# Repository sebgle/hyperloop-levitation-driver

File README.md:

# Hyperloop Levitation Coil Driver

A two-channel H-bridge driver for the levitation coils on a hyperloop pod. It takes PWM from the
pod's control computer and switches 60 V into two coils at up to 30 A each, roughly 1.8 kW per
coil. Two boards drive the pod's four coils.

Design work for the levitation subsystem of a student hyperloop pod. The levitation team set the
requirements. The schematic, board layout, documentation and verification scripts are mine. This
repository holds the KiCad 10 project along with the design notes, the reviews, and the scripts
that check the layout.

**Status: schematic done and verified. Placement done. Routing under way.**

## Requirements

| | |
|---|---|
| Bus | 60 V max, battery fed |
| Current | 30 A per coil by design. The team's stated minimum is 60 A across all four |
| Coil | About 2 Ω and 10 mH, unmeasured |
| PWM | 16 kHz now, 32 kHz ceiling |
| Control | PID runs on a separate MCU. This board takes PWM and a shutdown line |
| Grounding | Coils float. Only common point is the motor controller negatives |
| Rails | Pod supplies 12 V, 5 V and 3.3 V |

## The board

| | |
|---|---|
| Size | 160 × 140 mm, 4 layers, 2 oz outer / 1 oz inner |
| Parts | 184 footprints, 99 nets, 492 pads |
| FETs | 8 × IRF100B201, 100 V, 4.2 mΩ, TO-220 on a shared heatsink |
| Gate drive | 4 × IR2184, bootstrap high side |
| Sensing | 0.5 mΩ shunt in line with each coil, INA240A2 amplifier |
| Protection | ±45 A window comparator into a latch on the driver shutdown pin |
| Bus | 6 × 470 µF, ceramics at each bridge, TVS clamp |
| Connectors | Molex 38969-0002, 50 A, takes 8 AWG |

## Design decisions

### Modulation

Four transistors form an H-bridge with the coil across the middle. Which pair is switched on
decides what the coil sees.

The board cycles through these states thousands of times a second. What sets the average voltage
across the coil is which states it cycles between, and how long it holds each one.

There are two ways to pick that sequence:

```
locked antiphase   Q1+Q4 -> Q2+Q3 -> Q1+Q4 -> Q2+Q3    coil sees  +60 V, -60 V, +60 V, -60 V
unipolar           Q1+Q4 -> Q1+Q3 -> Q1+Q4 -> Q1+Q3    coil sees  +60 V,   0 V, +60 V,   0 V
```

Antiphase only uses the top two rows of the table, so the coil gets slammed between +60 V and
−60 V every cycle even when you want very little current out of it. Unipolar swaps one of those
for a freewheel row, where both ends of the coil are held at the same voltage. Nothing is
pushing the current any more, so it coasts around a loop through the two transistors and fades
slowly, the way a bike wheel spins on after you stop pedalling. A switching cycle is far too
short for it to fade much. That halves the voltage swing, and at low output the coil spends most
of each cycle coasting.

That keeps the current steadier and takes a lot of strain off the bus capacitors, which is what
decided it. A levitation coil sits near zero most of the time, so low output is its normal
operating point.

The tradeoff is that the four transistors no longer share the work evenly. Two do most of it and
run hot, two do very little and stay cool. They are arranged alternately on the heatsink so no
two hot ones sit next to each other.

### Four layers

A four-layer board costs more than a two-layer one, and the usual justification for the extra
layers, less resistance in the copper, did not apply. The power traces here are already wide
enough, and a third copper layer would save about 3 W out of 54 W.

The real reason is what sits underneath the transistors. On a four-layer board a solid ground
layer sits 0.2 mm below them instead of 1.44 mm away on the other side of the board. Current
returning through that nearby layer takes a much tighter path, which shrinks the voltage spikes
the transistors see each time they switch. The same layer shields the small measurement signals
from the 30 A being chopped a couple of centimetres away.

### Current sensing

Each coil's current is measured across a very small resistor, half a milliohm, which turns 30 A
into about 15 millivolts. An amplifier scales that up fifty times to something the rest of the
circuit can work with. The resistor sits in the wire feeding the coil rather than in the ground
return, because current in a levitation coil flows in both directions and this is the only
position that sees both. TI's application note SBOA174 covers why this amplifier suits the job.

### Overcurrent protection

If coil current passes 45 A in either direction, a comparator trips and a latch shuts the gate
drivers off and holds them off until the microcontroller clears it. Without the latch the fault
would clear itself the moment current dropped, and the board would switch on and off
repeatedly. The comparator takes 1.3 microseconds to react, which sounded far too slow until I
worked out how fast the current can actually change: the coil's inductance limits it to about
13 milliamps in that time. The genuinely fast failure is both transistors in one leg turning on
together, and the gate driver chips block that on their own.

## Checking the layout

Instead of trusting measurements written down by hand, a script reads the board file and
recalculates them. Every spacing and clearance figure quoted in the documentation comes out of
it, and it runs in about a second.

```
courtyard overlaps: 0
CH1 A   12.9 mm    CH1 B   16.7 mm
CH2 A   12.9 mm    CH2 B   16.7 mm
heatsink-shadow intrusions: none
```

The wiring was also checked against the connection list exported from the schematic, separately
from KiCad's own checker, and matched exactly on all 99 nets and 492 pads. Two rules that used
to live in a document now live in the board's rule file, so the software refuses to let me break
them: high-current nets have to be poured as wide copper areas rather than drawn as thin traces,
and the inner ground layer stays solid.

## Assumptions

Some inputs to this design were never measured, so every assumption is written down with what
happens if it turns out wrong. The full list, A1 to A16, is in `docs/09_design_sheet_rev0.md`.
Three of them matter:

- **A1**: the coil is 2 Ω. If it is really 4 Ω, the board can only push half the current and the
  high-side gate drive stops working. Nobody has put a meter on it yet.
- **A9**: 60 V is the maximum, not the normal running voltage. If it is the normal voltage, a
  full battery sits closer to 67 V and the 100 V parts get uncomfortably close to their limit.
- **A16**: the power traces are 10.7 mm wide. That figure comes from an older standard, and the
  project notes already say it should be rechecked against the current one.

## Mistakes and what they changed

**Measured the wrong thing.** Six large capacitors were supposed to fit between the two coil
connectors. Comparing the metal pads, they fit. Comparing the space each part actually needs
around it, they did not, because the connector needs far more room than its pads suggest. The
board grew from 160 × 100 to 160 × 140 mm, and I rewrote the checker to use the real keep-out
areas.

**Dropped a digit.** The board file said the copper was 0.007 mm thick instead of 0.07 mm.
Nothing inside KiCad depended on it, but it would have gone to the manufacturer, and at that
thickness the power traces would have run ten times hotter than intended.

**Trusted a number that looked deliberate.** The high-current traces were set to 3 mm wide,
which looks like a real power width. At 30 A that works out to roughly a 160 °C rise. It needed
about eight times more copper than that. The same setting had also caught ground, so all 119
ground pads inherited it.

**Reviewed in the wrong order.** Three rounds of review found 19, then 5, then 14 problems, and
about 40 % of the last round came from fixes made in the first two. Patching a design whose main
input is still unmeasured creates problems faster than review finds them, so I stopped and moved
on to layout.

## Repository layout

```
final_lev.kicad_*                KiCad project and its custom design rules
lib.pretty/                      custom connector footprint
tools/lay.py                     the layout checker
docs/00_design_log.md            running log, including the corrections
docs/01_reference_library.md     every datasheet and app note used, each one checked
docs/09_design_sheet_rev0.md     component values and the assumption list
docs/16_adversarial_review.md    38 review findings across three rounds
docs/18_firmware_interface.md    what the control microcontroller has to send
docs/20_layout_phase.md          placement and the verified clearances
docs/21_stackup_and_layers.md    layer stackup and routing order
```

## Not done

- Routing. The inner ground layer is poured, nothing else is.
- The coil has never been measured. Once it is, several numbers have to be redone together,
  because they all depend on it: ripple, transistor heating, heatsink size, gate drive supply
  and trip timing.
- Some heat calculations in `docs/09` were done under the older switching scheme.
- The bus fault detector is specified and not designed.
- `docs/09` still lists an older set of current-sense parts. The schematic is right and that
  document is stale.

## Running it

KiCad 10 on Windows. The scripts are Python 3, standard library only. From the project root:

```powershell
py tools\lay.py
```

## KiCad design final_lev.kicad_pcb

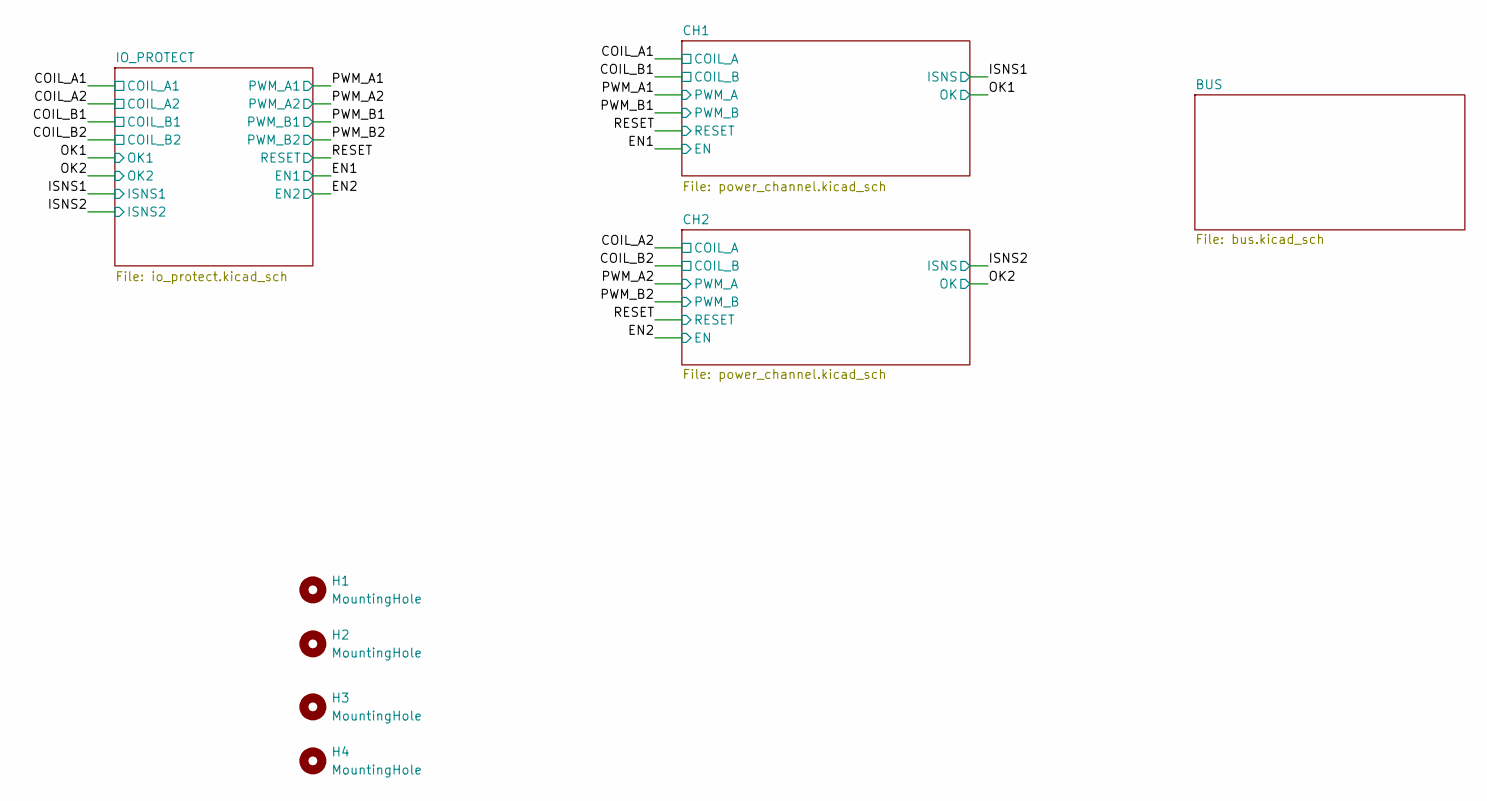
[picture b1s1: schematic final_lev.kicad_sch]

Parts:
H1, H2, H3, H4: MountingHole; MountingHole_3.2mm_M3_Pad

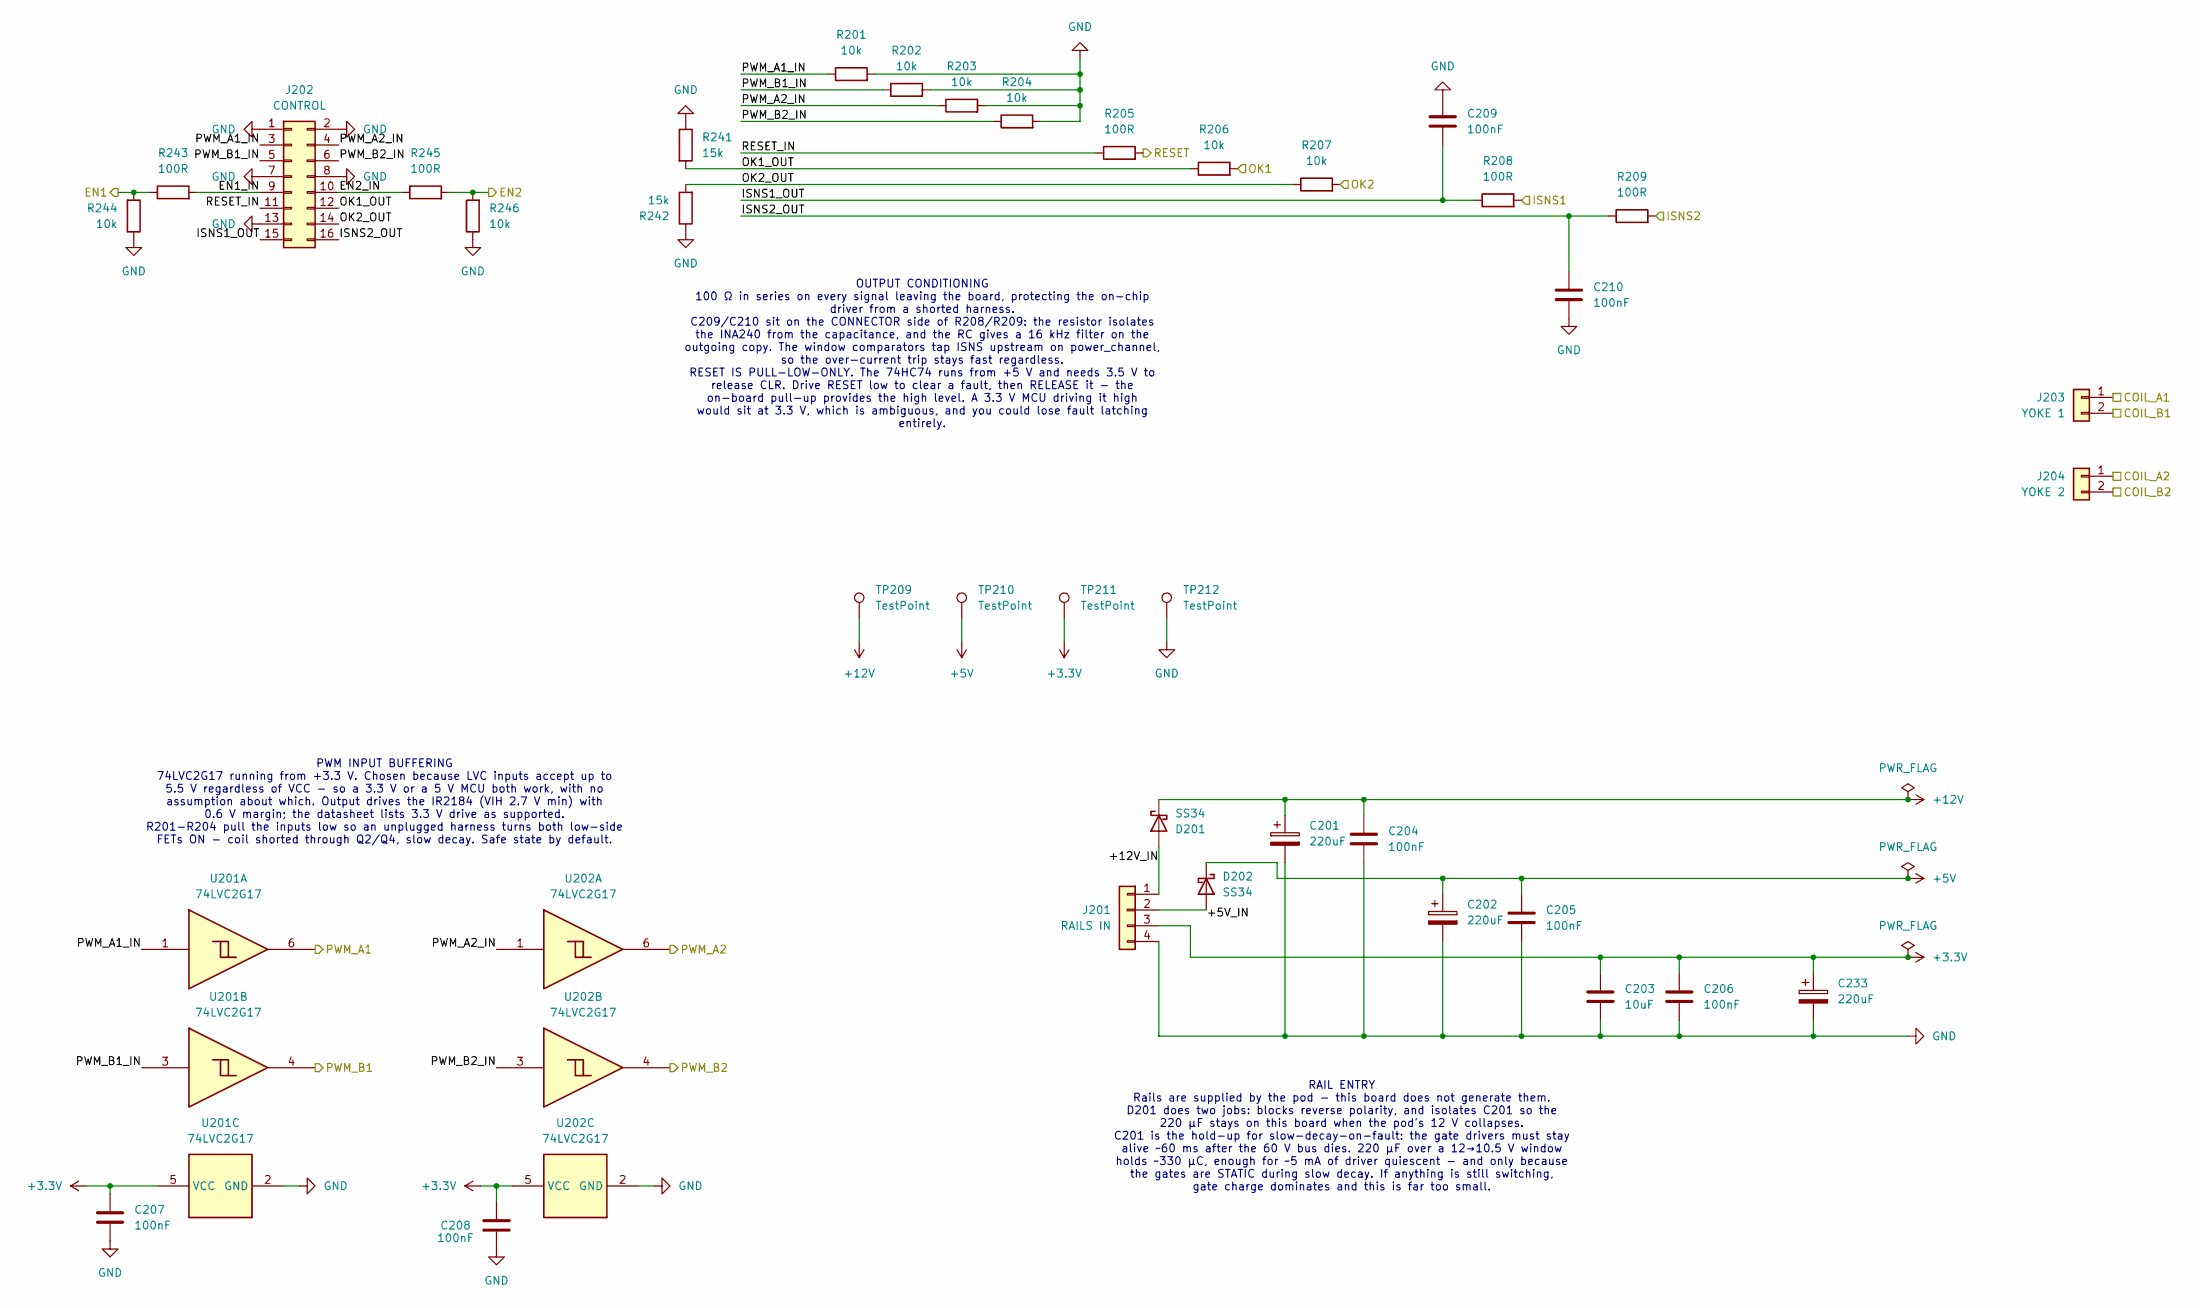
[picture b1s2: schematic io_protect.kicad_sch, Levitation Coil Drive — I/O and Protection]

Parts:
C201, C202, C233: 220uF; CP_Radial_D8.0mm_P3.50mm; Voltage 25V
C203: 10uF; C_1206_3216Metric_Pad1.33x1.80mm_HandSolder; Voltage 25V
C204, C205, C206, C207, C208, C209, C210: 100nF; C_0805_2012Metric_Pad1.18x1.45mm_HandSolder; Voltage 25V
D201, D202: SS34; D_SMA_Handsoldering
J201: RAILS IN; Molex_Micro-Fit_3.0_43650-0400_1x04_P3.00mm_Horizontal; MPN 43650-0400
J202: CONTROL; Molex_Micro-Fit_3.0_43045-1600_2x08_P3.00mm_Horizontal; MPN 43045-1600
J203: YOKE 1; 389690002; MPN 38969-0002
J204: YOKE 2; 389690002; MPN 38969-0002
R201, R202, R203, R204, R206, R207, R244, R246: 10k; R_0805_2012Metric_Pad1.20x1.40mm_HandSolder
R205, R208, R209, R243, R245: 100R; R_0805_2012Metric_Pad1.20x1.40mm_HandSolder
R241, R242: 15k; R_0805_2012Metric_Pad1.20x1.40mm_HandSolder
TP209, TP210, TP211, TP212: TestPoint; TestPoint_Loop_D2.50mm_Drill1.0mm
U201, U202: 74LVC2G17; SOT-23-6

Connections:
+3.3V: C203.1, C206.1, C207.1, C208.1, C233.1, J201.3, TP211.1 (1_1), U201.5 (VCC), U202.5 (VCC); also elsewhere on the board
+5V: C202.1, C205.1, D202.1 (K), TP210.1 (1_1); also elsewhere on the board
+12V: C201.1, C204.1, D201.1 (K), TP209.1 (1_1); also elsewhere on the board
/COIL_A1: J203.1; also elsewhere on the board
/COIL_A2: J204.1; also elsewhere on the board
/COIL_B1: J203.2; also elsewhere on the board
/COIL_B2: J204.2; also elsewhere on the board
/EN1: R243.1, R244.2; also elsewhere on the board
/EN2: R245.2, R246.2; also elsewhere on the board
/IO_PROTECT/+5V_IN: D202.2 (A), J201.2
/IO_PROTECT/+12V_IN: D201.2 (A), J201.1
/IO_PROTECT/EN1_IN: J202.9, R243.2
/IO_PROTECT/EN2_IN: J202.10, R245.1
/IO_PROTECT/ISNS1_OUT: C209.2, J202.15, R208.1
/IO_PROTECT/ISNS2_OUT: C210.1, J202.16, R209.1
/IO_PROTECT/OK1_OUT: J202.12, R206.1, R241.2
/IO_PROTECT/OK2_OUT: J202.14, R207.1, R242.2
/IO_PROTECT/PWM_A1_IN: J202.3, R201.1, U201.1
/IO_PROTECT/PWM_A2_IN: J202.4, R203.1, U202.1
/IO_PROTECT/PWM_B1_IN: J202.5, R202.1, U201.3
/IO_PROTECT/PWM_B2_IN: J202.6, R204.1, U202.3
/IO_PROTECT/RESET_IN: J202.11, R205.1
/ISNS1: R208.2; also elsewhere on the board
/ISNS2: R209.2; also elsewhere on the board
/OK1: R206.2; also elsewhere on the board
/OK2: R207.2; also elsewhere on the board
/PWM_A1: U201.6; also elsewhere on the board
/PWM_A2: U202.6; also elsewhere on the board
/PWM_B1: U201.4; also elsewhere on the board
/PWM_B2: U202.4; also elsewhere on the board
/RESET: R205.2; also elsewhere on the board
GND: C201.2, C202.2, C203.2, C204.2, C205.2, C206.2, C207.2, C208.2, C209.1, C210.2, C233.2, J201.4, J202.1, J202.2, J202.7, J202.8, J202.13, R201.2, R202.2, R203.2, R204.2, R241.1, R242.1, R244.1, R246.1, TP212.1 (1_1), U201.2 (GND), U202.2 (GND); also elsewhere on the board

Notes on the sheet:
PWM INPUT BUFFERING 74LVC2G17 running from +3.3 V. Chosen because LVC inputs accept up to 5.5 V regardless of VCC - so a 3.3 V or a 5 V MCU both work, with no assumption about which. Output drives the IR2184 (VIH 2.7 V min) with 0.6 V margin; the datasheet lists 3.3 V drive as supported. R201-R204 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
RAIL ENTRY Rails are supplied by the pod - this board does not generate them. D201 does two jobs: blocks reverse polarity, and isolates C201 so the 220 µF stays on this board when the pod's 12 V collapses. C201 is the hold-up for slow-decay-on-fault: the gate drivers must stay alive ~60 ms after th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
OUTPUT CONDITIONING 100 Ω in series on every signal leaving the board, protecting the on-chip driver from a shorted harness. C209/C210 sit on the CONNECTOR side of R208/R209: the resistor isolates the INA240 from the capacitance, and the RC gives a 16 kHz filter on the outgoing copy. The window com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

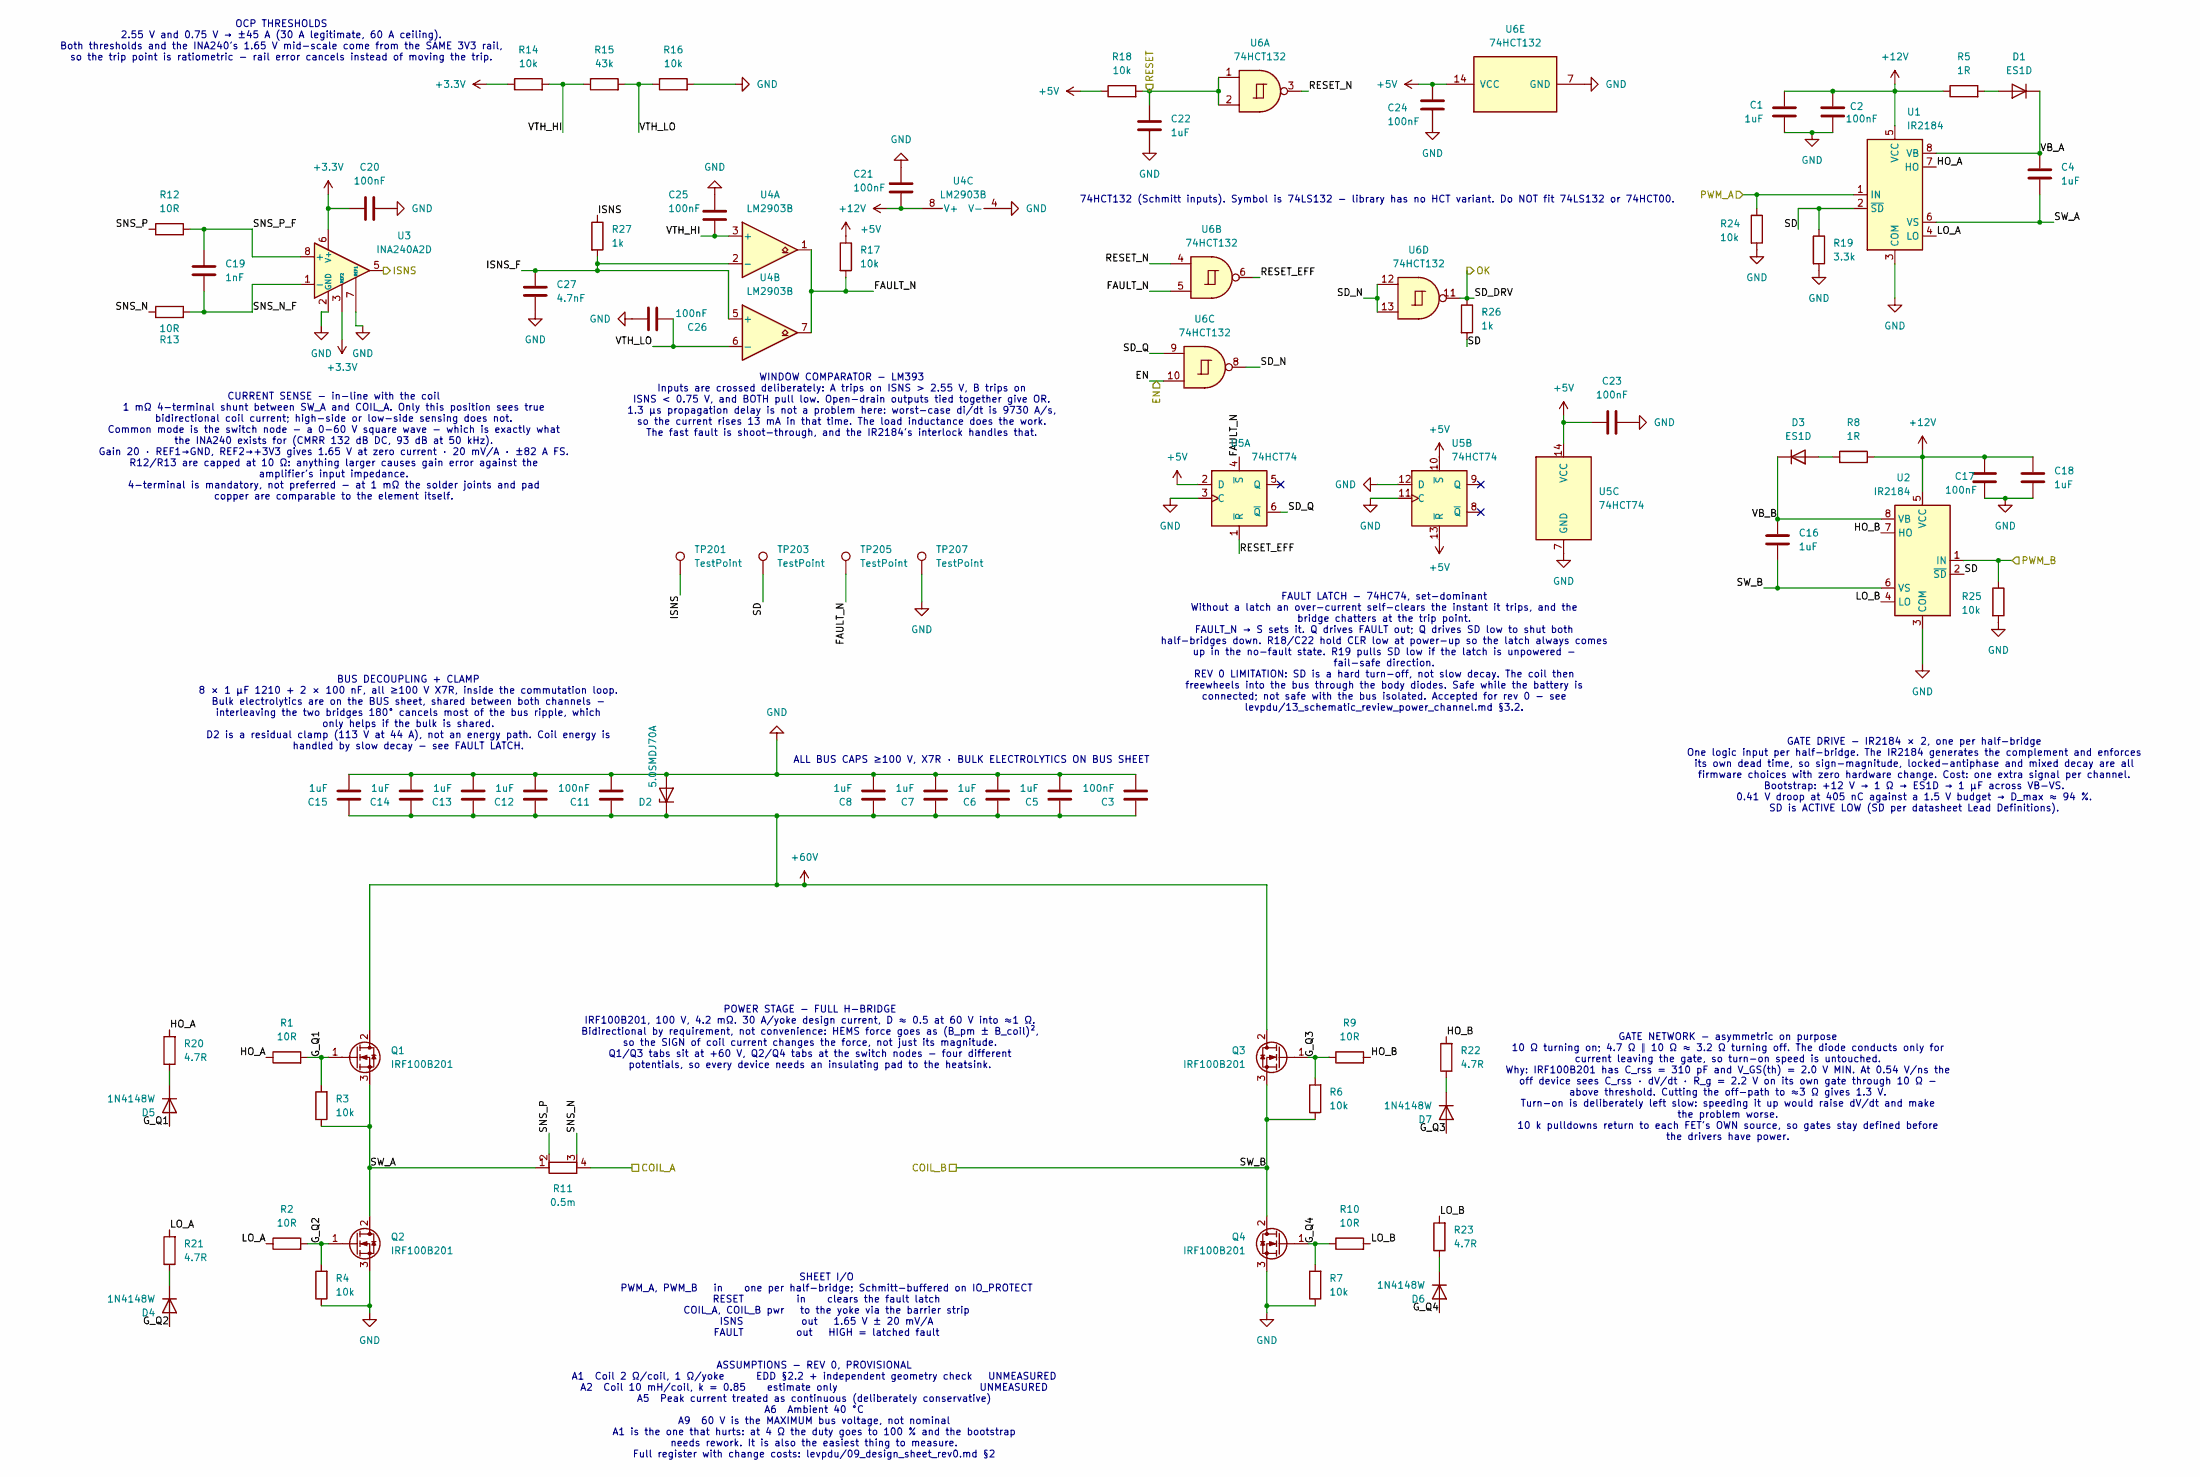
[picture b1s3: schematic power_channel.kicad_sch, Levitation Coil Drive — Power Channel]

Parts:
C1, C4, C16, C18, C22: 1uF; C_0805_2012Metric_Pad1.18x1.45mm_HandSolder; Voltage 25V
C2, C3, C11, C17, C20, C21, C23: 100nF; C_0805_2012Metric_Pad1.18x1.45mm_HandSolder; Voltage 100V
C5, C6, C7, C8, C12, C13, C14, C15: 1uF; C_1210_3225Metric_Pad1.33x2.70mm_HandSolder; Voltage 100V
C19: 1nF; C_0805_2012Metric_Pad1.18x1.45mm_HandSolder; Voltage 50V
C24, C25, C26: 100nF; C_0805_2012Metric_Pad1.18x1.45mm_HandSolder; Voltage 25V
C27: 4.7nF; C_0805_2012Metric_Pad1.18x1.45mm_HandSolder; Voltage 50V
D1, D3: ES1D; D_SMA_Handsoldering
D2: 5.0SMDJ70A; D_SMC_Handsoldering
D4, D5, D6, D7: 1N4148W; D_SOD-123
Q1, Q2, Q3, Q4: IRF100B201; TO-220-3_Vertical; MPN IRF100B201
R1, R2, R9, R10: 10R; R_1206_3216Metric_Pad1.30x1.75mm_HandSolder
R3, R4, R6, R7, R17, R18, R24, R25: 10k; R_0805_2012Metric_Pad1.20x1.40mm_HandSolder
R5, R8: 1R; R_0805_2012Metric_Pad1.20x1.40mm_HandSolder
R11: 0.5m; R_Shunt_Vishay_WSK2512_6332Metric_T2.66mm; Tolerance 1%; MPN WSK2512L5000FEA
R12, R13: 10R; R_0805_2012Metric_Pad1.20x1.40mm_HandSolder
R14, R16: 10k; R_0805_2012Metric_Pad1.20x1.40mm_HandSolder; Tolerance 1%
R15: 43k; R_0805_2012Metric_Pad1.20x1.40mm_HandSolder; Tolerance 1%
R19: 3.3k; R_0805_2012Metric_Pad1.20x1.40mm_HandSolder
R20, R21, R22, R23: 4.7R; R_0805_2012Metric_Pad1.20x1.40mm_HandSolder
R26, R27: 1k; R_0805_2012Metric_Pad1.20x1.40mm_HandSolder
TP201, TP203, TP205, TP207: TestPoint; TestPoint_Loop_D2.50mm_Drill1.0mm
U1, U2: IR2184; SOIC-8_3.9x4.9mm_P1.27mm; MPN IR2184SPBF
U3: INA240A2D; SOIC-8_3.9x4.9mm_P1.27mm
U4: LM2903B; SOIC-8_3.9x4.9mm_P1.27mm; MPN LM2903BDR
U5: 74HCT74; SOIC-14_3.9x8.7mm_P1.27mm
U6: 74HCT132; SOIC-14_3.9x8.7mm_P1.27mm; MPN 74HCT132D,653

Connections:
+3.3V: C20.1, R14.1, U3.3 (REF2), U3.6 (V+); also elsewhere on the board
+5V: C23.1, C24.1, R17.1, R18.1, U5.2 (D), U5.10 (~S), U5.13 (~R), U5.14 (VCC), U6.14 (VCC); also elsewhere on the board
+12V: C1.1, C2.1, C17.1, C18.1, C21.2, R5.1, R8.1, U1.5 (VCC), U2.5 (VCC), U4.8 (V+); also elsewhere on the board
+60V: C3.1, C5.1, C6.1, C7.1, C8.1, C11.1, C12.1, C13.1, C14.1, C15.1, D2.1 (K), Q1.2 (D), Q3.2 (D); also elsewhere on the board
/CH1/FAULT_N: R17.2, TP205.1 (1_1), U4.1, U4.7, U5.4 (~S), U6.5
/CH1/G_Q1: D5.2 (A), Q1.1 (G), R1.2, R3.2
/CH1/G_Q2: D4.2 (A), Q2.1 (G), R2.2, R4.2
/CH1/G_Q3: D7.2 (A), Q3.1 (G), R6.2, R9.1
/CH1/G_Q4: D6.2 (A), Q4.1 (G), R7.2, R10.1
/CH1/HO_A: R1.1, R20.2, U1.7 (HO)
/CH1/HO_B: R9.2, R22.2, U2.7 (HO)
/CH1/ISNS_F: C27.1, R27.2, U4.2 (-), U4.5 (+)
/CH1/LO_A: R2.1, R21.2, U1.4 (LO)
/CH1/LO_B: R10.2, R23.2, U2.4 (LO)
/CH1/RESET_EFF: U5.1 (~R), U6.6
/CH1/RESET_N: U6.3, U6.4
/CH1/SD: R19.1, R26.2, TP203.1 (1_1), U1.2 (~SD), U2.2 (~SD)
/CH1/SD_N: U6.8, U6.12, U6.13
/CH1/SD_Q: U5.6 (~Q), U6.9
/CH1/SNS_N: R11.3, R13.1
/CH1/SNS_N_F: C19.2, R13.2, U3.1 (-)
/CH1/SNS_P: R11.2, R12.1
/CH1/SNS_P_F: C19.1, R12.2, U3.8 (+)
/CH1/SW_A: C4.2, Q1.3 (S), Q2.2 (D), R3.1, R11.1, U1.6 (VS)
/CH1/VB_A: C4.1, D1.1 (K), U1.8 (VB)
/CH1/VB_B: C16.1, D3.1 (K), U2.8 (VB)
/CH1/VTH_HI: C25.2, R14.2, R15.1, U4.3 (+)
/CH1/VTH_LO: C26.2, R15.2, R16.1, U4.6 (-)
/COIL_A1: R11.4; also elsewhere on the board
/COIL_B1: C16.2, Q3.3 (S), Q4.2 (D), R6.1, U2.6 (VS); also elsewhere on the board
/EN1: U6.10; also elsewhere on the board
/ISNS1: R27.1, TP201.1 (1_1), U3.5; also elsewhere on the board
/OK1: R26.1, U6.11; also elsewhere on the board
/PWM_A1: R24.1, U1.1 (IN); also elsewhere on the board
/PWM_B1: R25.1, U2.1 (IN); also elsewhere on the board
/RESET: C22.1, R18.2, U6.1, U6.2; also elsewhere on the board
GND: C1.2, C2.2, C3.2, C5.2, C6.2, C7.2, C8.2, C11.2, C12.2, C13.2, C14.2, C15.2, C17.2, C18.2, C20.2, C21.1, C22.2, C23.2, C24.2, C25.1, C26.1, C27.2, D2.2 (A), Q2.3 (S), Q4.3 (S), R4.1, R7.1, R16.2, R19.2, R24.2, R25.2, TP207.1 (1_1), U1.3 (COM), U2.3 (COM), U3.2 (GND), U3.4 (GND), U3.7 (REF1), U4.4 (V-), U5.3 (C), U5.7 (GND), U5.11 (C), U5.12 (D), U6.7 (GND); also elsewhere on the board
unnamed: D1.2 (A), R5.2
unnamed: D3.2 (A), R8.2
unnamed: D4.1 (K), R21.1
unnamed: D5.1 (K), R20.1
unnamed: D6.1 (K), R23.1
unnamed: D7.1 (K), R22.1

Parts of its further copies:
C211: 1nF; C_0805_2012Metric_Pad1.18x1.45mm_HandSolder; Voltage 50V
C212, C214, C215, C216, C219, C220, C221, C222: 1uF; C_1210_3225Metric_Pad1.33x2.70mm_HandSolder; Voltage 100V
C213, C217, C218, C223, C225, C228, C229: 100nF; C_0805_2012Metric_Pad1.18x1.45mm_HandSolder; Voltage 100V
C224, C226, C227, C230, C231: 1uF; C_0805_2012Metric_Pad1.18x1.45mm_HandSolder; Voltage 25V
C232, C235, C237: 100nF; C_0805_2012Metric_Pad1.18x1.45mm_HandSolder; Voltage 25V
C239: 4.7nF; C_0805_2012Metric_Pad1.18x1.45mm_HandSolder; Voltage 50V
D203, D204, D206, D207: 1N4148W; D_SOD-123
D205: 5.0SMDJ70A; D_SMC_Handsoldering
D208, D209: ES1D; D_SMA_Handsoldering
Q201, Q202, Q203, Q204: IRF100B201; TO-220-3_Vertical; MPN IRF100B201
R210, R211: 10R; R_0805_2012Metric_Pad1.20x1.40mm_HandSolder
R212, R213, R228, R229: 4.7R; R_0805_2012Metric_Pad1.20x1.40mm_HandSolder
R214, R215, R226, R227: 10R; R_1206_3216Metric_Pad1.30x1.75mm_HandSolder
R216, R217, R222, R223, R224, R225, R236, R238: 10k; R_0805_2012Metric_Pad1.20x1.40mm_HandSolder
R218, R221: 10k; R_0805_2012Metric_Pad1.20x1.40mm_HandSolder; Tolerance 1%
R219: 0.5m; R_Shunt_Vishay_WSK2512_6332Metric_T2.66mm; Tolerance 1%; MPN WSK2512L5000FEA
R220: 43k; R_0805_2012Metric_Pad1.20x1.40mm_HandSolder; Tolerance 1%
R230: 3.3k; R_0805_2012Metric_Pad1.20x1.40mm_HandSolder
R231, R232: 1R; R_0805_2012Metric_Pad1.20x1.40mm_HandSolder
R234, R240: 1k; R_0805_2012Metric_Pad1.20x1.40mm_HandSolder
TP202, TP204, TP206, TP208: TestPoint; TestPoint_Loop_D2.50mm_Drill1.0mm
U203: INA240A2D; SOIC-8_3.9x4.9mm_P1.27mm
U204: LM2903B; SOIC-8_3.9x4.9mm_P1.27mm; MPN LM2903BDR
U205: 74HCT74; SOIC-14_3.9x8.7mm_P1.27mm
U206, U207: IR2184; SOIC-8_3.9x4.9mm_P1.27mm; MPN IR2184SPBF
U208: 74HCT132; SOIC-14_3.9x8.7mm_P1.27mm; MPN 74HCT132D,653

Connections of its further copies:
+3.3V: C213.1, R218.1, U203.3 (REF2), U203.6 (V+); also elsewhere on the board
+5V: C225.1, C232.1, R222.1, R223.1, U205.2 (D), U205.10 (~S), U205.13 (~R), U205.14 (VCC), U208.14 (VCC); also elsewhere on the board
+12V: C218.2, C227.1, C228.1, C229.1, C230.1, R231.1, R232.1, U204.8 (V+), U206.5 (VCC), U207.5 (VCC); also elsewhere on the board
+60V: C212.1, C214.1, C215.1, C216.1, C217.1, C219.1, C220.1, C221.1, C222.1, C223.1, D205.1 (K), Q201.2 (D), Q203.2 (D); also elsewhere on the board
/CH2/FAULT_N: R222.2, TP206.1 (1_1), U204.1, U204.7, U205.4 (~S), U208.5
/CH2/G_Q1: D203.2 (A), Q201.1 (G), R214.2, R216.2
/CH2/G_Q2: D204.2 (A), Q202.1 (G), R215.2, R217.2
/CH2/G_Q3: D207.2 (A), Q203.1 (G), R224.2, R226.1
/CH2/G_Q4: D206.2 (A), Q204.1 (G), R225.2, R227.1
/CH2/HO_A: R212.2, R214.1, U206.7 (HO)
/CH2/HO_B: R226.2, R229.2, U207.7 (HO)
/CH2/ISNS_F: C239.1, R240.2, U204.2 (-), U204.5 (+)
/CH2/LO_A: R213.2, R215.1, U206.4 (LO)
/CH2/LO_B: R227.2, R228.2, U207.4 (LO)
/CH2/RESET_EFF: U205.1 (~R), U208.6
/CH2/RESET_N: U208.3, U208.4
/CH2/SD: R230.1, R234.2, TP204.1 (1_1), U206.2 (~SD), U207.2 (~SD)
/CH2/SD_N: U208.8, U208.12, U208.13
/CH2/SD_Q: U205.6 (~Q), U208.9
/CH2/SNS_N: R211.1, R219.3
/CH2/SNS_N_F: C211.2, R211.2, U203.1 (-)
/CH2/SNS_P: R210.1, R219.2
/CH2/SNS_P_F: C211.1, R210.2, U203.8 (+)
/CH2/SW_A: C231.2, Q201.3 (S), Q202.2 (D), R216.1, R219.1, U206.6 (VS)
/CH2/VB_A: C231.1, D209.1 (K), U206.8 (VB)
/CH2/VB_B: C226.1, D208.1 (K), U207.8 (VB)
/CH2/VTH_HI: C235.2, R218.2, R220.1, U204.3 (+)
/CH2/VTH_LO: C237.2, R220.2, R221.1, U204.6 (-)
/COIL_A2: R219.4; also elsewhere on the board
/COIL_B2: C226.2, Q203.3 (S), Q204.2 (D), R224.1, U207.6 (VS); also elsewhere on the board
/EN2: U208.10; also elsewhere on the board
/ISNS2: R240.1, TP202.1 (1_1), U203.5; also elsewhere on the board
/OK2: R234.1, U208.11; also elsewhere on the board
/PWM_A2: R236.1, U206.1 (IN); also elsewhere on the board
/PWM_B2: R238.1, U207.1 (IN); also elsewhere on the board
/RESET: C224.1, R223.2, U208.1, U208.2; also elsewhere on the board
GND: C212.2, C213.2, C214.2, C215.2, C216.2, C217.2, C218.1, C219.2, C220.2, C221.2, C222.2, C223.2, C224.2, C225.2, C227.2, C228.2, C229.2, C230.2, C232.2, C235.1, C237.1, C239.2, D205.2 (A), Q202.3 (S), Q204.3 (S), R217.1, R221.2, R225.1, R230.2, R236.2, R238.2, TP208.1 (1_1), U203.2 (GND), U203.4 (GND), U203.7 (REF1), U204.4 (V-), U205.3 (C), U205.7 (GND), U205.11 (C), U205.12 (D), U206.3 (COM), U207.3 (COM), U208.7 (GND); also elsewhere on the board
unnamed: D203.1 (K), R212.1
unnamed: D204.1 (K), R213.1
unnamed: D206.1 (K), R228.1
unnamed: D207.1 (K), R229.1
unnamed: D208.2 (A), R231.2
unnamed: D209.2 (A), R232.2

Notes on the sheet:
ALL BUS CAPS ≥100 V, X7R · BULK ELECTROLYTICS ON BUS SHEET
GATE DRIVE - IR2184 × 2, one per half-bridge One logic input per half-bridge. The IR2184 generates the complement and enforces its own dead time, so sign-magnitude, locked-antiphase and mixed decay are all firmware choices with zero hardware change. Cost: one extra signal per channel. Bootstrap: +1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
ASSUMPTIONS - REV 0, PROVISIONAL A1 Coil 2 Ω/coil, 1 Ω/yoke EDD §2.2 + independent geometry check UNMEASURED A2 Coil 10 mH/coil, k = 0.85 estimate only UNMEASURED A5 Peak current treated as continuous (deliberately conservative) A6 Ambient 40 °C A9 60 V is the MAXIMUM bus voltage, not nominal A1 is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
SHEET I/O PWM_A, PWM_B in one per half-bridge; Schmitt-buffered on IO_PROTECT RESET in clears the fault latch COIL_A, COIL_B pwr to the yoke via the barrier strip ISNS out 1.65 V ± 20 mV/A FAULT out HIGH = latched fault
74HCT132 (Schmitt inputs). Symbol is 74LS132 - library has no HCT variant. Do NOT fit 74LS132 or 74HCT00.
FAULT LATCH - 74HC74, set-dominant Without a latch an over-current self-clears the instant it trips, and the bridge chatters at the trip point. FAULT_N → S̄ sets it. Q drives FAULT out; Q̄ drives SD low to shut both half-bridges down. R18/C22 hold C̄L̄R̄ low at power-up so the latch always comes up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
GATE NETWORK - asymmetric on purpose 10 Ω turning on; 4.7 Ω ∥ 10 Ω ≈ 3.2 Ω turning off. The diode conducts only for current leaving the gate, so turn-on speed is untouched. Why: IRF100B201 has C_rss = 310 pF and V_GS(th) = 2.0 V MIN. At 0.54 V/ns the off device sees C_rss · dV/dt · R_g = 2.2 V on i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
POWER STAGE - FULL H-BRIDGE IRF100B201, 100 V, 4.2 mΩ. 30 A/yoke design current, D ≈ 0.5 at 60 V into ≈1 Ω. Bidirectional by requirement, not convenience: HEMS force goes as (B_pm ± B_coil)², so the SIGN of coil current changes the force, not just its magnitude. Q1/Q3 tabs sit at +60 V, Q2/Q4 tabs 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
WINDOW COMPARATOR - LM393 Inputs are crossed deliberately: A trips on ISNS > 2.55 V, B trips on ISNS < 0.75 V, and BOTH pull low. Open-drain outputs tied together give OR. 1.3 µs propagation delay is not a problem here: worst-case di/dt is 9730 A/s, so the current rises 13 mA in that time. The load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
BUS DECOUPLING + CLAMP 8 × 1 µF 1210 + 2 × 100 nF, all ≥100 V X7R, inside the commutation loop. Bulk electrolytics are on the BUS sheet, shared between both channels - interleaving the two bridges 180° cancels most of the bus ripple, which only helps if the bulk is shared. D2 is a residual clamp (1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
OCP THRESHOLDS 2.55 V and 0.75 V → ±45 A (30 A legitimate, 60 A ceiling). Both thresholds and the INA240's 1.65 V mid-scale come from the SAME 3V3 rail, so the trip point is ratiometric - rail error cancels instead of moving the trip.
CURRENT SENSE - in-line with the coil 1 mΩ 4-terminal shunt between SW_A and COIL_A. Only this position sees true bidirectional coil current; high-side or low-side sensing does not. Common mode is the switch node - a 0-60 V square wave - which is exactly what the INA240 exists for (CMRR 132 dB DC, 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

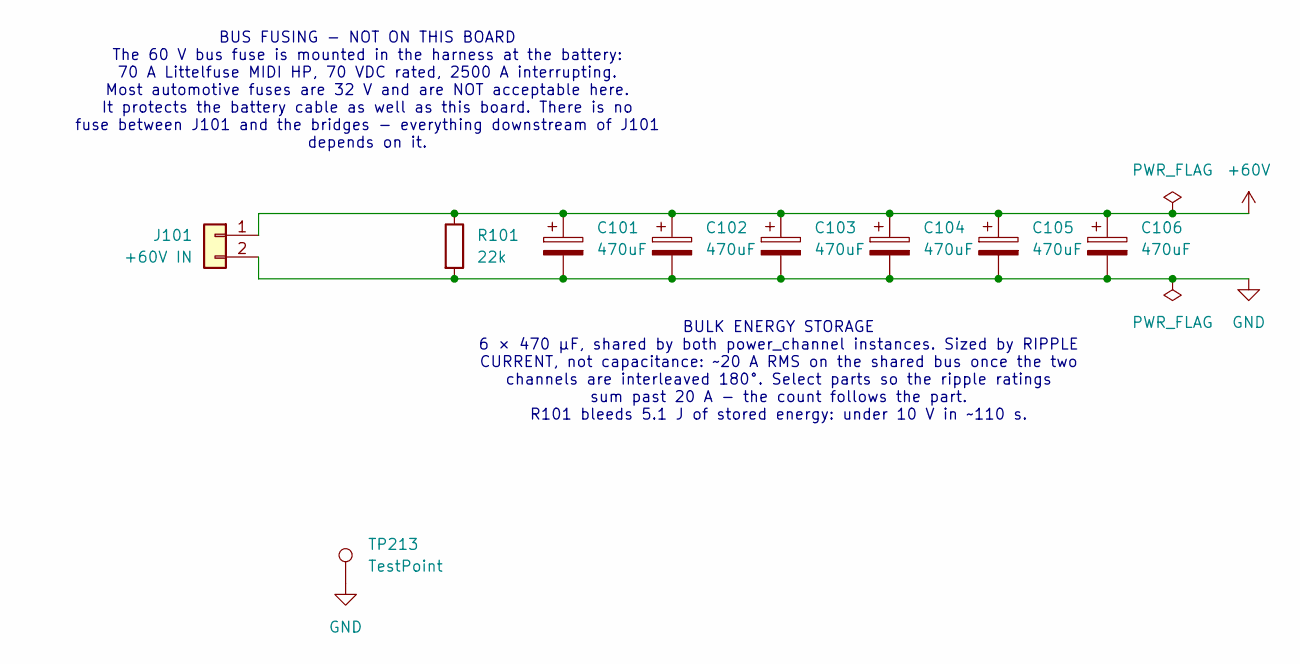
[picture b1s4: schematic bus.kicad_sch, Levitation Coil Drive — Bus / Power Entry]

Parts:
C101, C102, C103, C104, C105, C106: 470uF; CP_Radial_D16.0mm_P7.50mm; Voltage 100V; MPN 100ZLH470MEFC16X31.5
J101: +60V IN; 389690002; MPN 38969-0002
R101: 22k; R_2512_6332Metric
TP213: TestPoint; TestPoint_Loop_D2.50mm_Drill1.0mm

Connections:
+60V: C101.1, C102.1, C103.1, C104.1, C105.1, C106.1, J101.1, R101.1; also elsewhere on the board
GND: C101.2, C102.2, C103.2, C104.2, C105.2, C106.2, J101.2, R101.2, TP213.1 (1_1); also elsewhere on the board

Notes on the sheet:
BUS FUSING - NOT ON THIS BOARD The 60 V bus fuse is mounted in the harness at the battery: 70 A Littelfuse MIDI HP, 70 VDC rated, 2500 A interrupting. Most automotive fuses are 32 V and are NOT acceptable here. It protects the battery cable as well as this board. There is no fuse between J101 and t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
BULK ENERGY STORAGE 6 × 470 µF, shared by both power_channel instances. Sized by RIPPLE CURRENT, not capacitance: ~20 A RMS on the shared bus once the two channels are interleaved 180°. Select parts so the ripple ratings sum past 20 A - the count follows the part. R101 bleeds 5.1 J of stored energy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
